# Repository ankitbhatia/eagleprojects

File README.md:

# eagleprojects
My hobby eagle projects

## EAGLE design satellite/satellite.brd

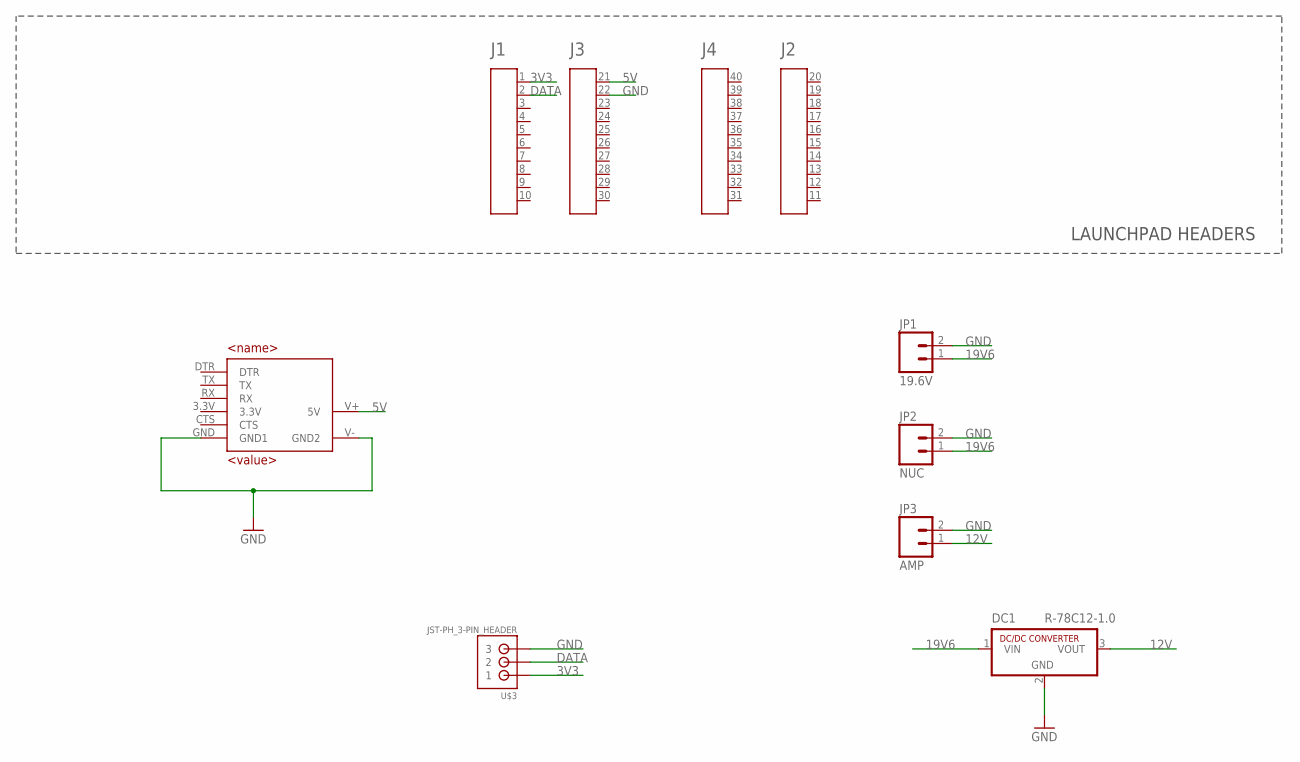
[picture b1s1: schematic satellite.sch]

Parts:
A1: HEADER4X10-BOOSTERPACK; 4X10-BOOSTERPACK
DC1: R-78C12-1.0; SIP3
JP1: 19.6V; SCREWTERMINAL-3.5MM-2
JP2: NUC; SCREWTERMINAL-3.5MM-2
JP3: AMP; SCREWTERMINAL-3.5MM-2
U1: 9DOF
U$3: JST-PH_3-PIN_HEADER; JST_B3B-PH_HEADER

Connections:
3V3: A1.1, U$3.P1 (1)
5V: A1.21, U1.V+ (5V)
12V: DC1.3 (VOUT), JP3.1
19V6: DC1.1 (VIN), JP1.1, JP2.1
DATA: A1.2, U$3.P2 (2)
GND: A1.22, DC1.2 (GND), JP1.2, JP2.2, JP3.2, U1.GND (GND1), U1.V- (GND2), U$3.P3 (3)

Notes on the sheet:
LAUNCHPAD HEADERS

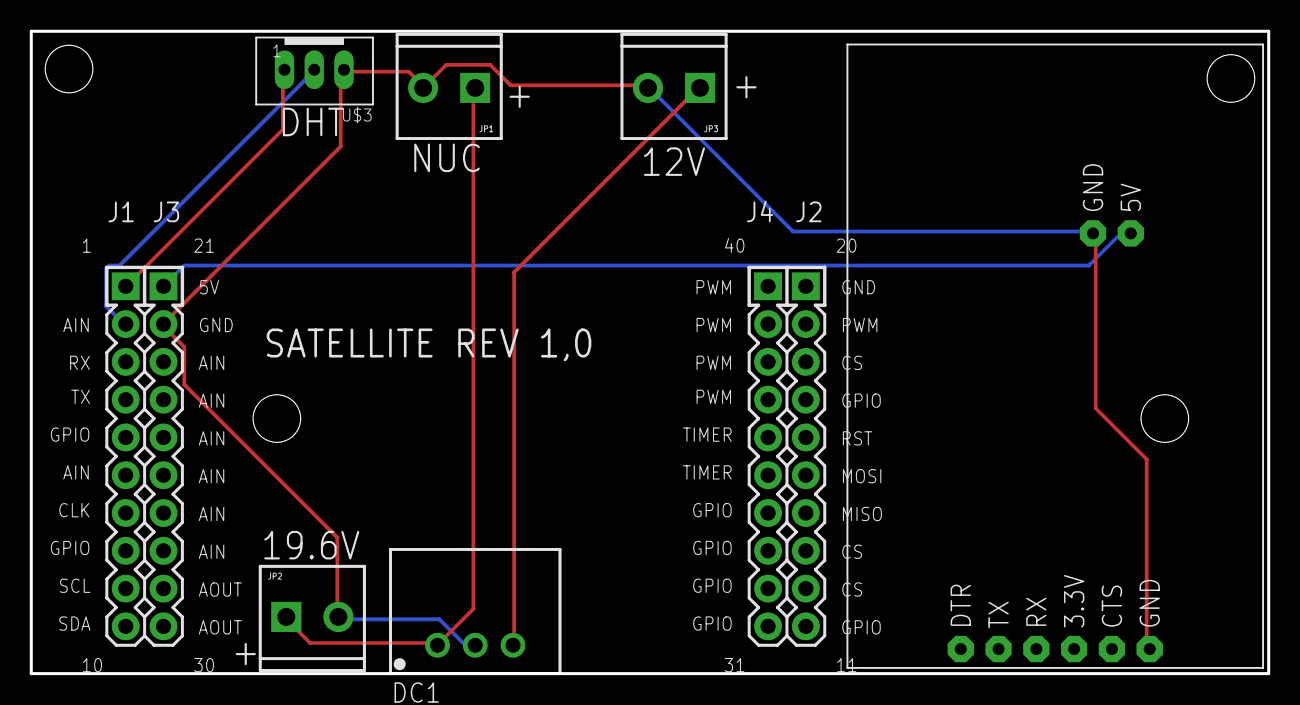
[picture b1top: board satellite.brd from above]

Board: 2 copper layers, 83.2 x 43.2 mm, 7 parts (0 on the bottom side), 6 nets.

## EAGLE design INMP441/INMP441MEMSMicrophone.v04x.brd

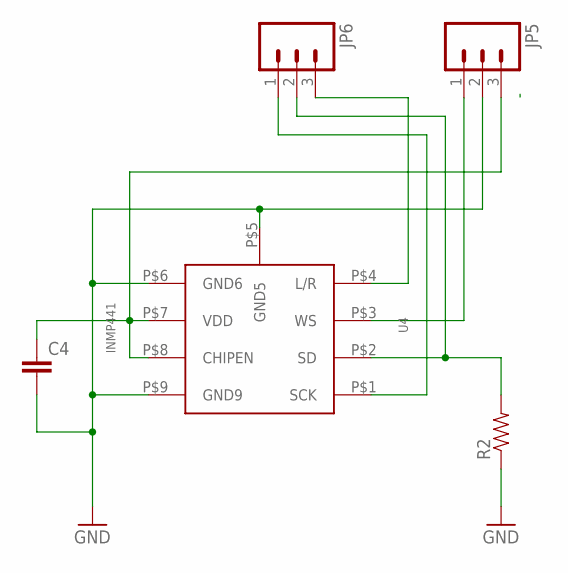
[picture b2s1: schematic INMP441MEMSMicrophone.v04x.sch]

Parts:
C4: CAP0402-CAP; 0402-CAP
JP5, JP6: M031X03_NO_SILK; 1X03_NO_SILK
R2: RESISTOR0402-RES; 0402-RES
U4: INMP441

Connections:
GND: C4.2, JP5.2, R2.1, U4.P$5 (GND5), U4.P$6 (GND6), U4.P$9 (GND9)
unnamed: JP6.3, U4.P$4 (L/R)
unnamed: JP5.1, U4.P$3 (WS)
unnamed: JP6.2, R2.2, U4.P$2 (SD)
unnamed: JP6.1, U4.P$1 (SCK)
unnamed: C4.1, JP5.3, U4.P$7 (VDD), U4.P$8 (CHIPEN)

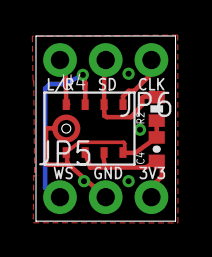
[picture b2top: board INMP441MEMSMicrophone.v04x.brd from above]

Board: 2 copper layers, 7.8 x 10.3 mm, 5 parts (0 on the bottom side), 6 nets.

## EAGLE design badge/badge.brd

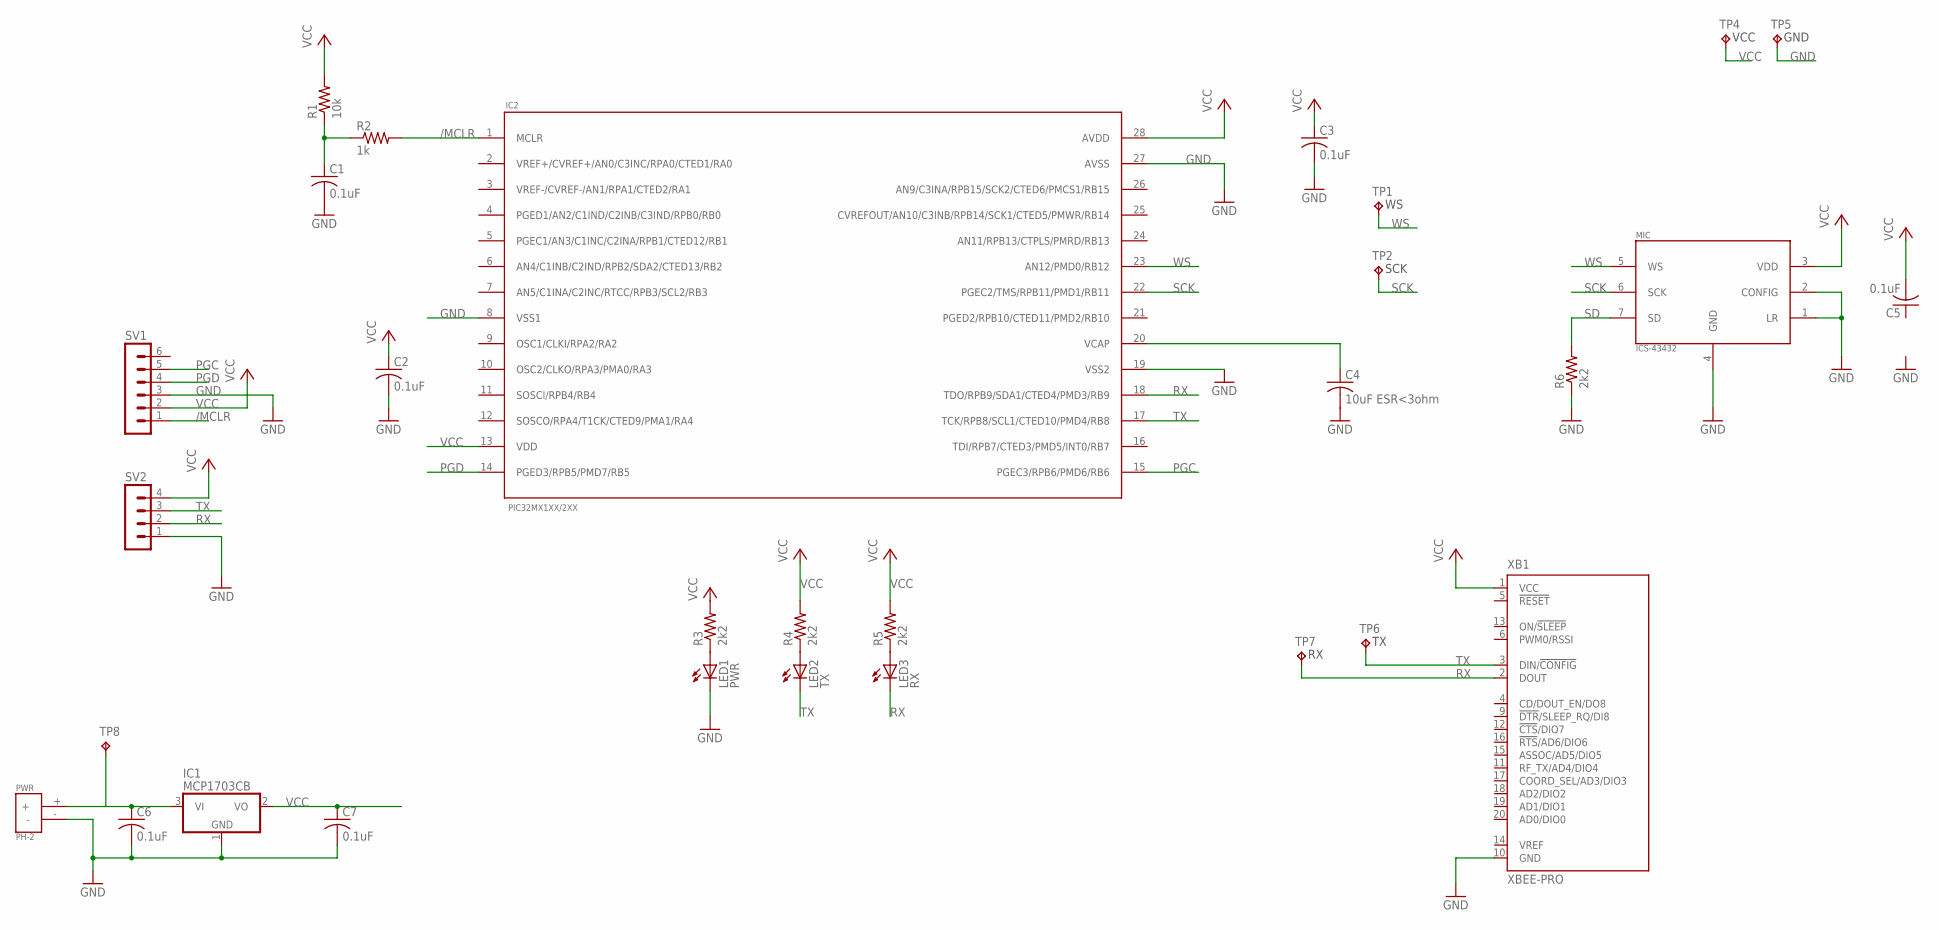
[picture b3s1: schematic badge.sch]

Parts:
C1, C2, C3, C5, C6, C7: 0.1uF; C0603
C4: 10uF ESR<3ohm; C0603
IC1: MCP1703CB; SOT23
IC2: PIC32MX1XX/2XX; SOIC-28
LED1: PWR; CHIP-LED0603
LED2: TX; CHIP-LED0603
LED3: RX; CHIP-LED0603
MIC: ICS-43432
PWR: PH-2
R1: 10k; R0603
R2: 1k; R0603
R3, R4, R5, R6: 2k2; R0603
SV1: MA06-1
SV2: MA04-1
TP1, TP2, TP4, TP5, TP6, TP7, TP8: TPPAD1-13; P1-13
XB1: XBEE-PRO

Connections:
/MCLR: IC2.1 (MCLR), R2.2, SV1.1
GND: C1.2, C2.2, C3.2, C4.2, C6.2, C7.2, IC1.1 (GND), IC2.8 (VSS1), IC2.19 (VSS2), IC2.27 (AVSS), LED1.C, MIC.1 (LR), MIC.2 (CONFIG), MIC.4 (GND), PWR.-, R6.1, SV1.3, SV2.1, TP5.TP, XB1.10 (GND)
unnamed: C1.1, R1.1, R2.1
unnamed: C4.1, IC2.20 (VCAP)
unnamed: LED1.A, R3.1
unnamed: LED2.A, R4.1
unnamed: LED3.A, R5.1
unnamed: C6.1, IC1.3 (VI), PWR.+, TP8.TP
PGC: IC2.15 (PGEC3/RPB6/PMD6/RB6), SV1.5
PGD: IC2.14 (PGED3/RPB5/PMD7/RB5), SV1.4
RX: IC2.18 (TDO/RPB9/SDA1/CTED4/PMD3/RB9), LED3.C, SV2.2, TP7.TP, XB1.2 (DOUT)
SCK: IC2.22 (PGEC2/TMS/RPB11/PMD1/RB11), MIC.6 (SCK), TP2.TP
SD: MIC.7 (SD), R6.2
TX: IC2.17 (TCK/RPB8/SCL1/CTED10/PMD4/RB8), LED2.C, SV2.3, TP6.TP, XB1.3 (DIN/!CONFIG)
VCC: C2.1, C3.1, C5.2, C7.1, IC1.2 (VO), IC2.13 (VDD), IC2.28 (AVDD), MIC.3 (VDD), R1.2, R3.2, R4.2, R5.2, SV1.2, SV2.4, TP4.TP, XB1.1 (VCC)
WS: IC2.23 (AN12/PMD0/RB12), MIC.5 (WS), TP1.TP

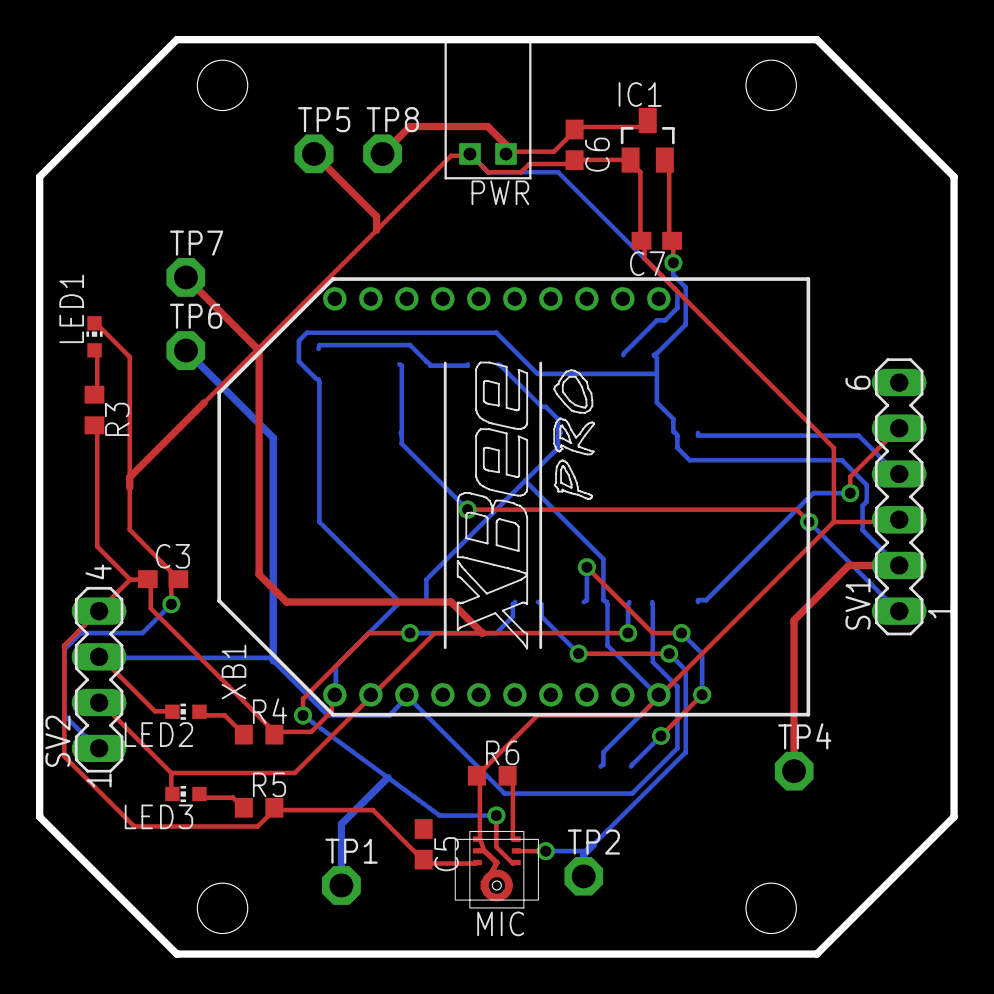
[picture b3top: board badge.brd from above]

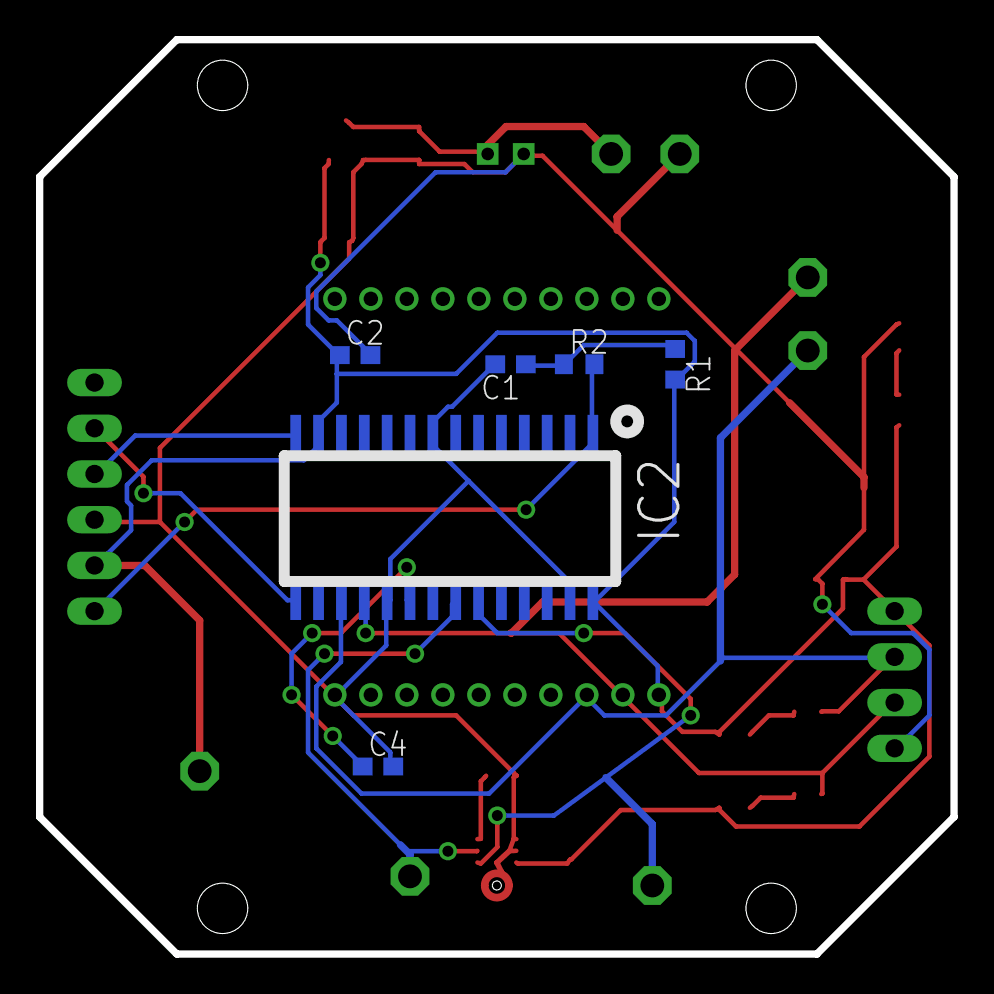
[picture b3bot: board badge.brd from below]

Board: 2 copper layers, 50.8 x 50.8 mm, 30 parts (6 on the bottom side), 16 nets.

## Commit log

2015-02-26 Started lightbar project
2015-06-03 Completed 2 projects

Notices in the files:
parts and their libraries:
SparkFun-Capacitors: Licensing: Creative Commons ShareAlike 4.0 International - https://creativecommons.org/licenses/by-sa/4.0
